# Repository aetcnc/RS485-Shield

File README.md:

RS485-Shield
============

An RS485 shield for Arduino which automatically handles RTS direction control with an on-chip state machine.

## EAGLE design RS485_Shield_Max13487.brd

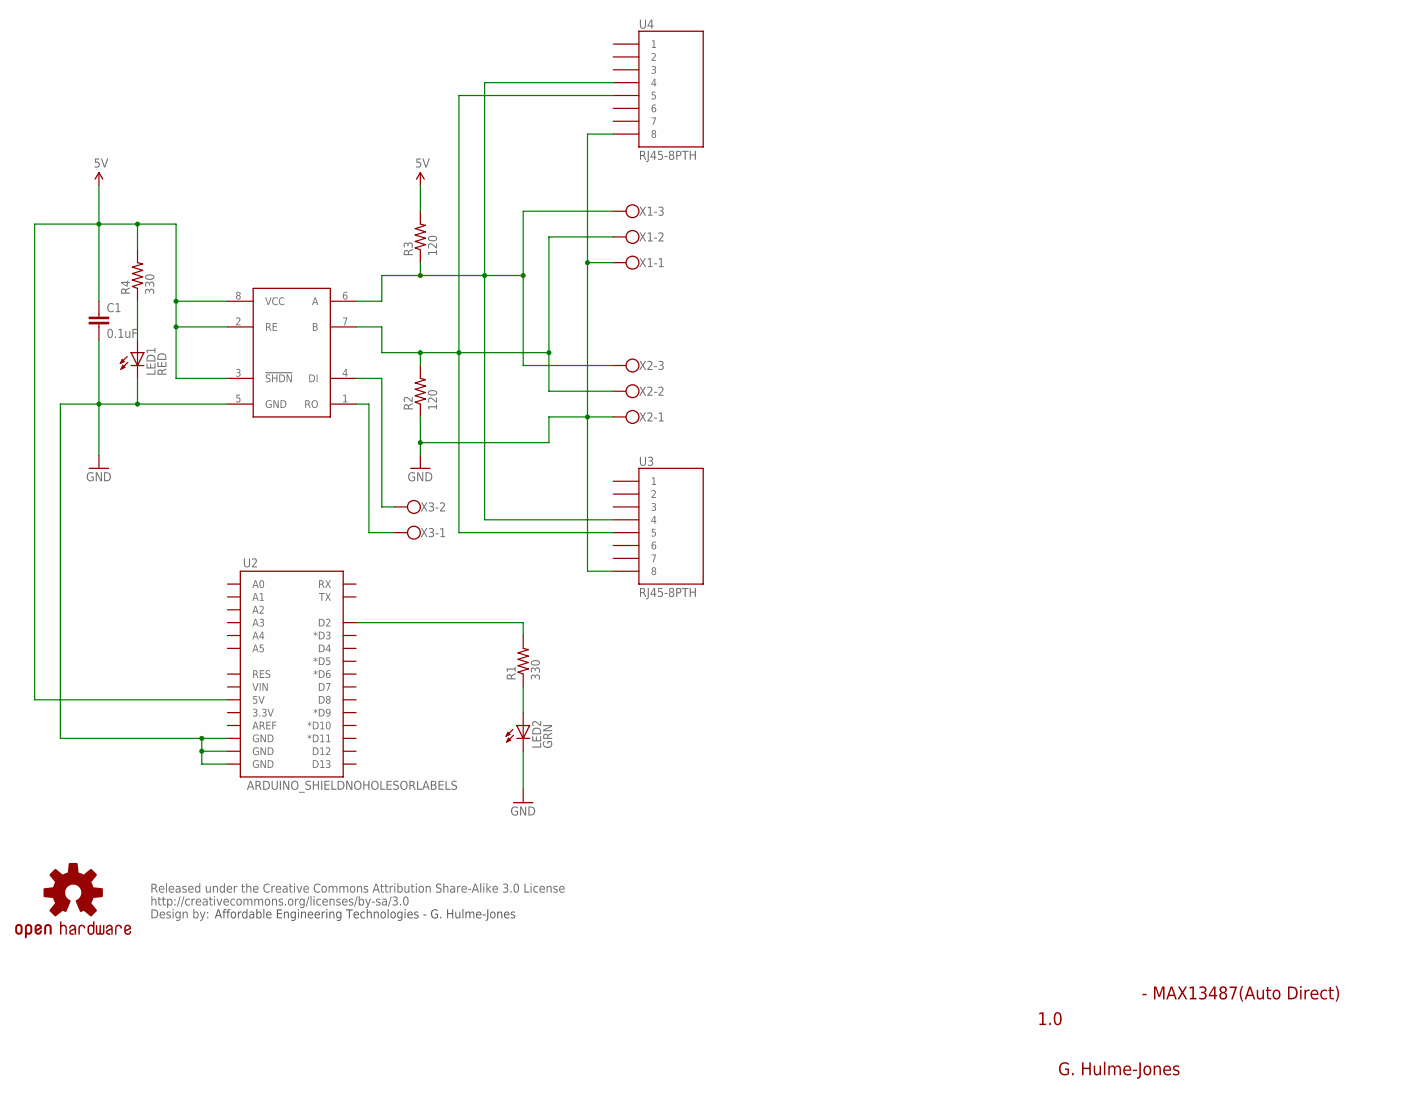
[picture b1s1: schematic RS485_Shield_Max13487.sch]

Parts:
C1: 0.1uF; 0402-CAP
CC_TEXT1: CREATIVE_COMMONS
LED1: RED; LED-0603
LED2: GRN; LED-0603
LOGO1: OSHW-LOGOL; OSHW-LOGO-L
R1, R4: 330; 0402-RES
R2, R3: 120; 0402-RES
U1: MAX13487
U2: ARDUINO_SHIELDNOHOLESORLABELS; DUEMILANOVE_SHIELD_NOHOLES_NOLABELS
U3, U4: RJ45-8PTH; RJ45-8
X1, X2: W237-103
X3: W237-102

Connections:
5V: C1.1, R3.2, R4.2, U1.2 (RE), U1.3 (!SHDN), U1.8 (VCC), U2.5V
GND: C1.2, LED1.C, LED2.C, R2.1, U1.5 (GND), U2.GND@0 (GND), U2.GND@1 (GND), U2.GND@2 (GND), U3.8, U4.8, X1.1, X2.1
unnamed: LED1.A, R4.1
unnamed: R3.1, U1.6 (A), U3.4, U4.4, X1.3, X2.3
unnamed: R2.2, U1.7 (B), U3.5, U4.5, X1.2, X2.2
unnamed: LED2.A, R1.1
unnamed: R1.2, U2.D2
unnamed: U1.4 (DI), X3.2
unnamed: U1.1 (RO), X3.1

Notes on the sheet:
G. Hulme-Jones
1.0
- MAX13487(Auto Direct)
Affordable Engineering Technologies - G. Hulme-Jones

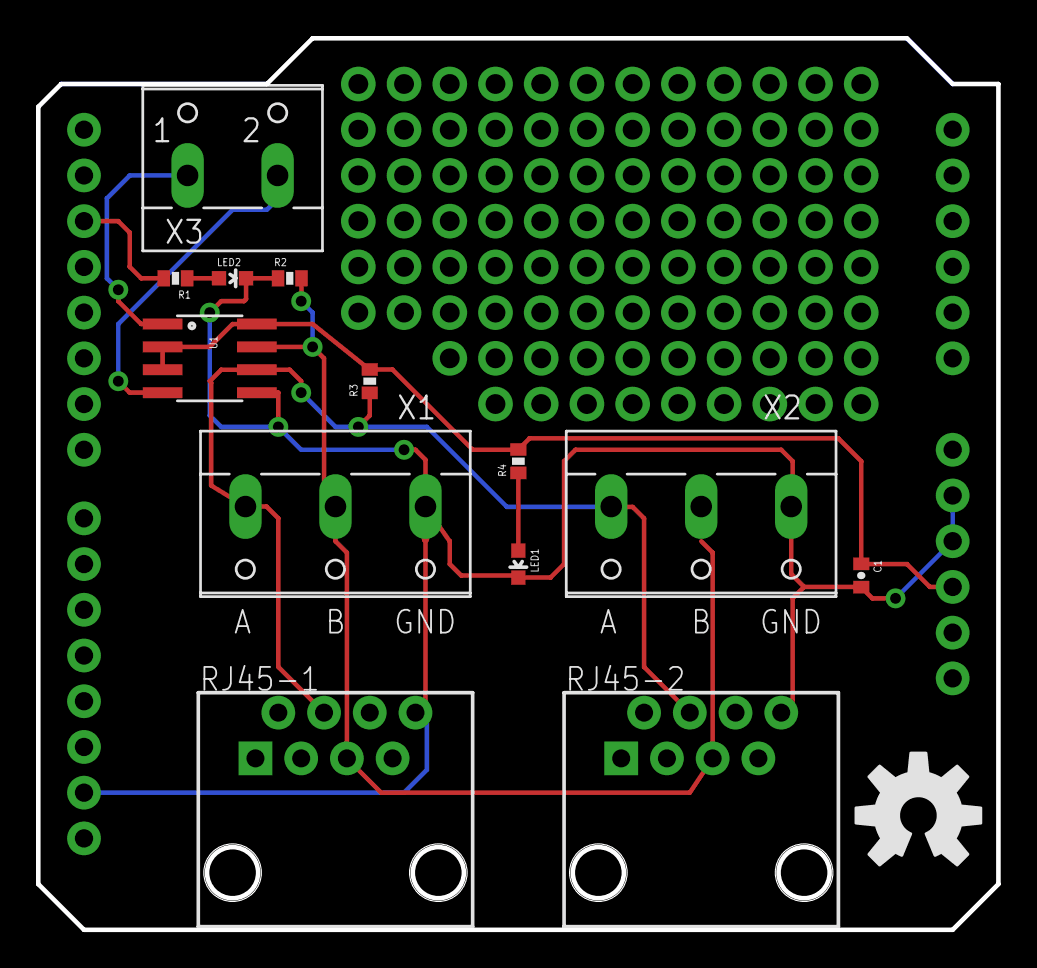
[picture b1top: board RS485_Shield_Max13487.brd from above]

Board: 2 copper layers, 53.3 x 49.5 mm, 16 parts (0 on the bottom side), 9 nets.

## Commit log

2013-12-24 Max13487 chip datasheet
    Reference document for technical specs of Max13487 chip
2013-12-24 Eagle Board and Schematic files uploaded
    Version 1.0 eagle files for public resource added for initial comment
    and discussion.
2013-12-24 Overview drawing showing RS485 shield features
    Overview drawing added to highlight features of the RS485 shield which
    are not obvious in the Eagle Files.
2013-12-24 Amended SimpleModbusMaster library files uploaded
    Modified the original SimpleModbusMasterV10 library from arduino.cc.
    Minimal changes made other than to define serial ports explicitly in
    code.
2014-01-08 None

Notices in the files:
parts and their libraries:
SparkFun-LED: Licensing: CC v3.0 Share-Alike You are welcome to use this library for commercial purposes.
SparkFun-Aesthetics: Released under the Creative Commons Attribution Share-Alike 3.0 License
SparkFun-Aesthetics: http://creativecommons.org/licenses/by-sa/3.0
